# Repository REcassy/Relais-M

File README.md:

This repo contains the schematics (KiCad + symbols/footprints), pcb (gerber + drill) files necessary to build a clone Relais M adapter for the Cassy Mobile as described here: https://recassy.github.io/2024/08/24/Relais-Clone.html

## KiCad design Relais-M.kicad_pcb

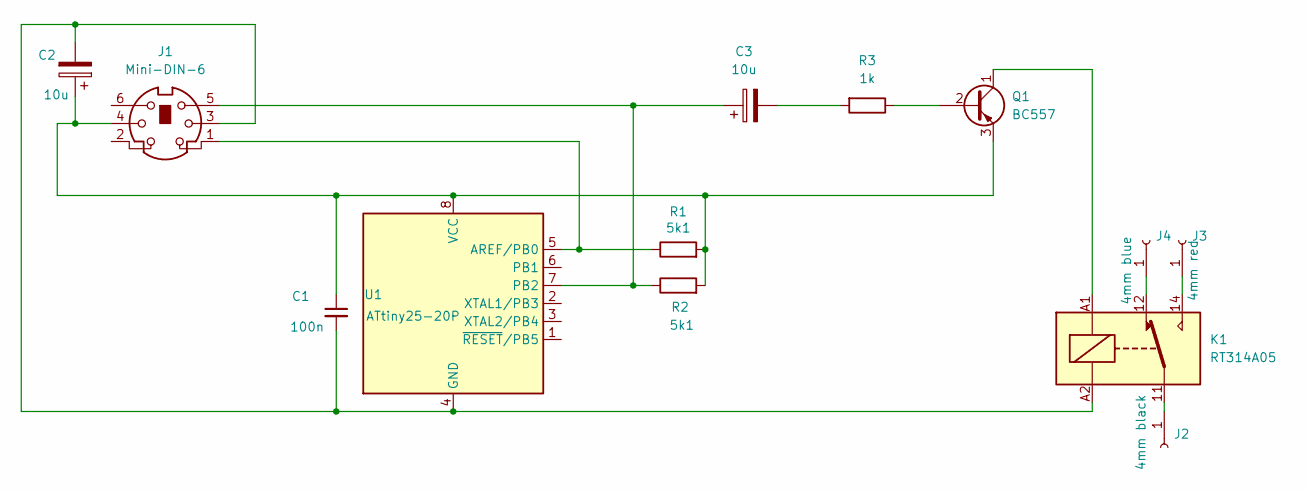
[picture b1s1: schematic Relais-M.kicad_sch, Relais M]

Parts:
C1: 100n; CP_Radial_Tantal_D4.5mm_P2.50mm
C2, C3: 10u; CP_Radial_D4.0mm_P2.00mm
J1: Mini-DIN-6; Connector_Mini-DIN_Female_6Pin_2rows
J2: 4mm black; Banana-Slot
J3: 4mm red; Banana-Slot
J4: 4mm blue; Banana-Slot
K1: RT314A05; Relay_SPDT_Schrack-RT1-16A-FormC_RM5mm
Q1: BC557; TO-92_Inline
R1, R2: 5k1; R_Axial_DIN0207_L6.3mm_D2.5mm_P10.16mm_Horizontal
R3: 1k; R_Axial_DIN0207_L6.3mm_D2.5mm_P10.16mm_Horizontal
U1: ATtiny25-20P; DIP-8_W7.62mm

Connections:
unnamed: C3.2, R3.2
unnamed: J2.1, K1.11
unnamed: J3.1, K1.14
unnamed: J4.1, K1.12
unnamed: Q1.2 (B), R3.1
unnamed: K1.A1, Q1.1 (C)
unnamed: C1.1, C2.1, J1.4, Q1.3 (E), R1.2, R2.2, U1.8 (VCC)
unnamed: J1.1, R1.1, U1.5 (AREF/PB0)
unnamed: C1.2, C2.2, J1.3, K1.A2, U1.4 (GND)
unnamed: C3.1, J1.5, R2.1, U1.7 (PB2)

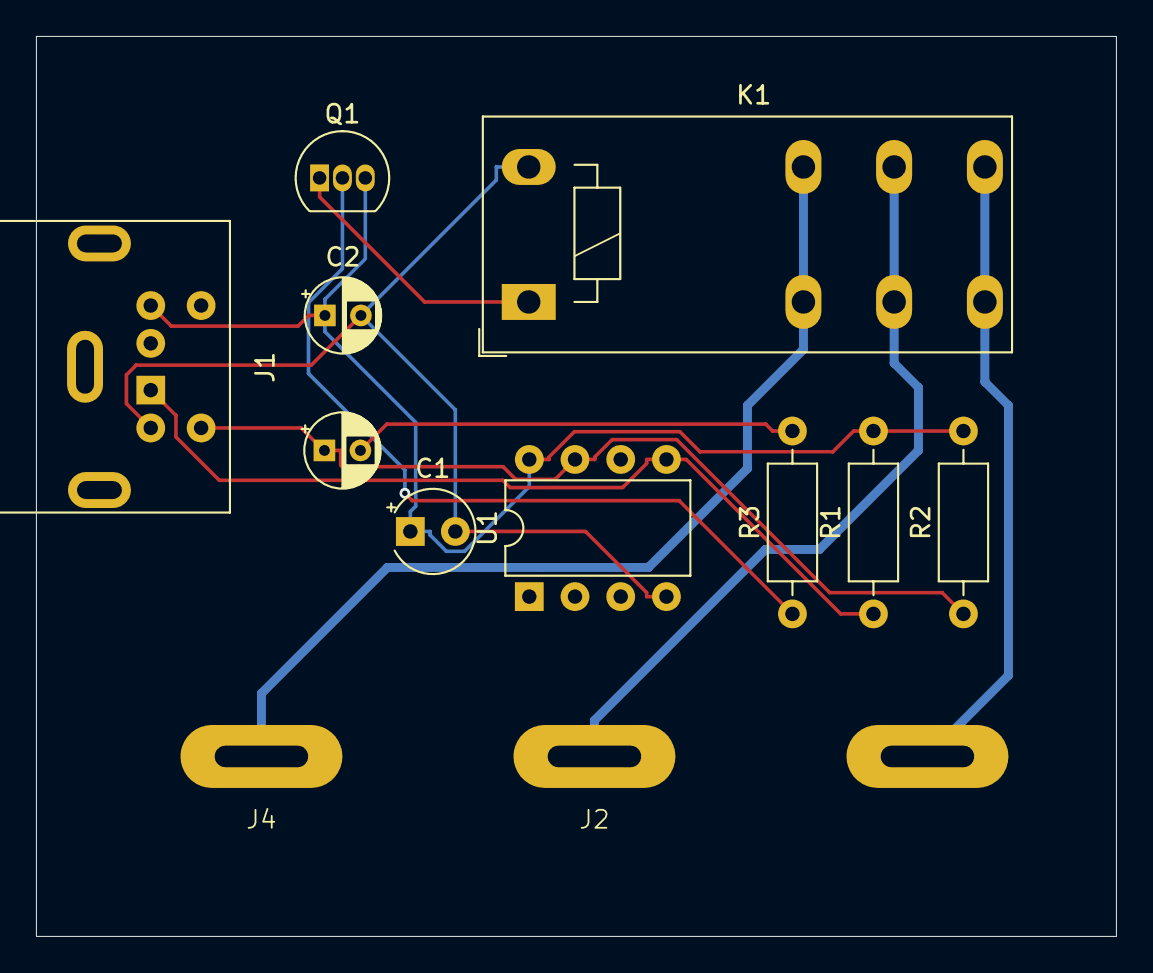
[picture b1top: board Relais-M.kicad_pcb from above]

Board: 2 copper layers, 60.0 x 50.0 mm, 13 parts (0 on the bottom side), 10 nets.
